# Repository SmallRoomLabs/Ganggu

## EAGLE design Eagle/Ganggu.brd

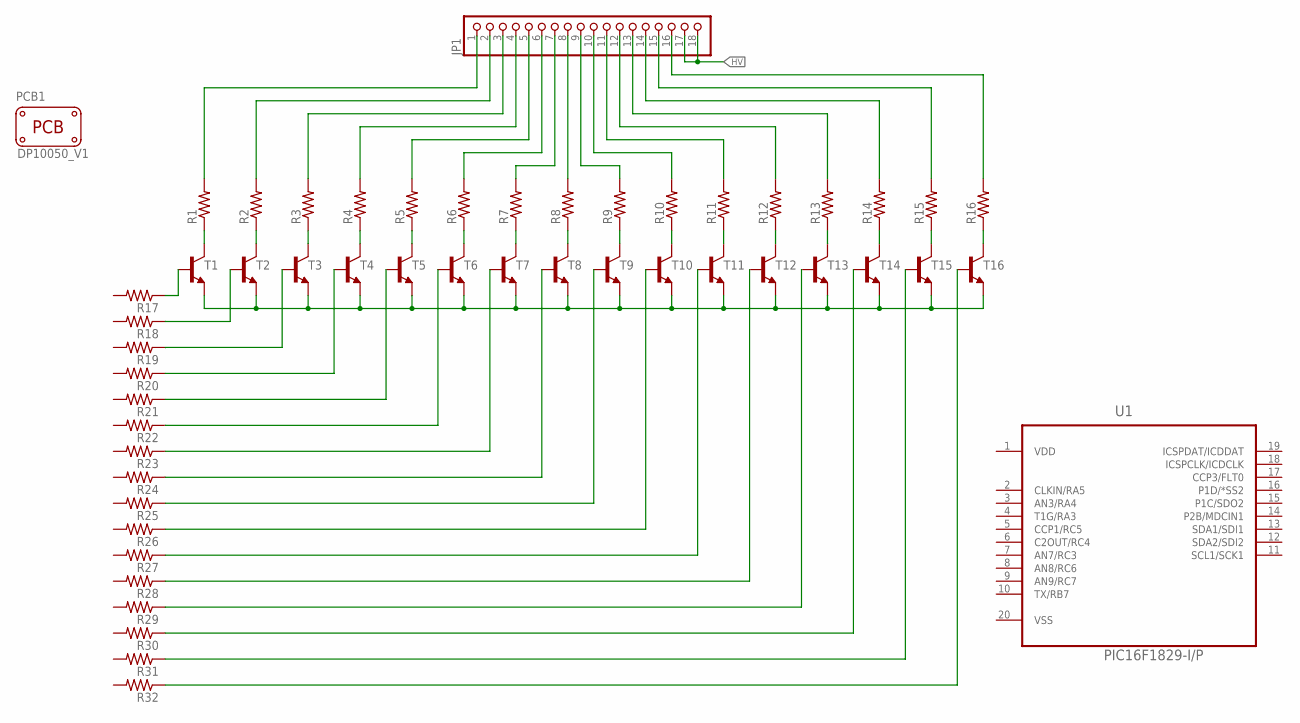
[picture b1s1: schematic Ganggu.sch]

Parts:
JP1: PINHD-1X18; 1X18
PCB1: PCB_DP_RECTANGLE-50X100; DP10050_V1
R1, R2, R3, R4, R5, R6, R7, R8, R9, R10, R11, R12, R13, R14, R15, R16, R17, R18, R19, R20, R21, R22, R23, R24, R25, R26, R27, R28, R29, R30, R31, R32: R-US_0207/9; 0207/9
T1, T2, T3, T4, T5, T6, T7, T8, T9, T10, T11, T12, T13, T14, T15, T16: 2N2222; TO92-EBC-OVAL
U1: PIC16F1829-I/P; DIP254P762X508-20P

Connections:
HV: JP1.17, JP1.18
unnamed: T1.E, T2.E, T3.E, T4.E, T5.E, T6.E, T7.E, T8.E, T9.E, T10.E, T11.E, T12.E, T13.E, T14.E, T15.E, T16.E
unnamed: R1.1, T1.C
unnamed: R2.1, T2.C
unnamed: R3.1, T3.C
unnamed: R18.1, T2.B
unnamed: R4.1, T4.C
unnamed: R5.1, T5.C
unnamed: R6.1, T6.C
unnamed: R19.1, T3.B
unnamed: R7.1, T7.C
unnamed: R8.1, T8.C
unnamed: R9.1, T9.C
unnamed: R17.1, T1.B
unnamed: R10.1, T10.C
unnamed: R20.1, T4.B
unnamed: R11.1, T11.C
unnamed: R12.1, T12.C
unnamed: R13.1, T13.C
unnamed: R21.1, T5.B
unnamed: R14.1, T14.C
unnamed: R22.1, T6.B
unnamed: R15.1, T15.C
unnamed: R16.1, T16.C
unnamed: R23.1, T7.B
unnamed: R24.1, T8.B
unnamed: R25.1, T9.B
unnamed: R26.1, T10.B
unnamed: R27.1, T11.B
unnamed: R28.1, T12.B
unnamed: R29.1, T13.B
unnamed: R30.1, T14.B
unnamed: R31.1, T15.B
unnamed: R32.1, T16.B
unnamed: JP1.1, R1.2
unnamed: JP1.2, R2.2
unnamed: JP1.3, R3.2
unnamed: JP1.4, R4.2
unnamed: JP1.5, R5.2
unnamed: JP1.6, R6.2
unnamed: JP1.7, R7.2
unnamed: JP1.8, R8.2
unnamed: JP1.9, R9.2
unnamed: JP1.10, R10.2
unnamed: JP1.11, R11.2
unnamed: JP1.12, R12.2
unnamed: JP1.13, R13.2
unnamed: JP1.14, R14.2
unnamed: JP1.15, R15.2
unnamed: JP1.16, R16.2
VDD: U1.1 (VDD)
VSS: U1.20 (VSS)

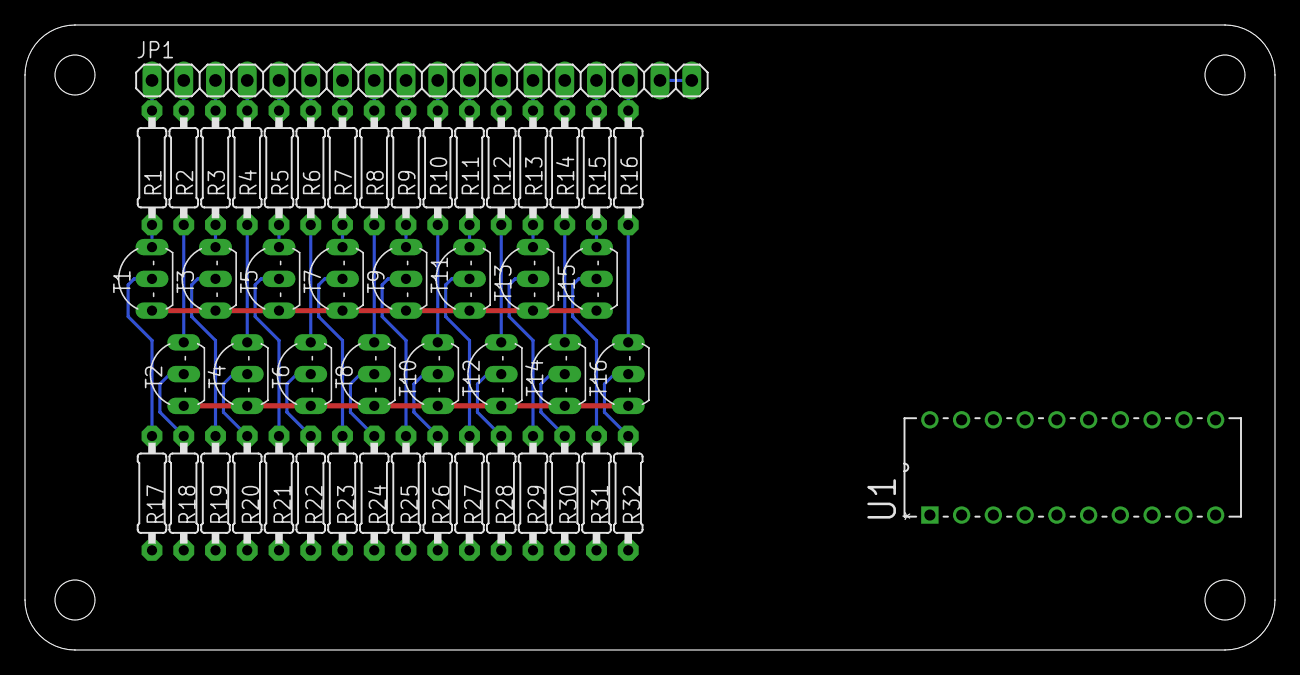
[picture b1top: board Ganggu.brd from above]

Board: 2 copper layers, 100.0 x 50.0 mm, 51 parts (0 on the bottom side), 50 nets.

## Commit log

2015-02-23 Added code for testing the hardware
2015-02-23 Start of schemtics
2015-02-23 More PCB works
